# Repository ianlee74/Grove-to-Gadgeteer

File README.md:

Grove-to-Gadgeteer
==================

A project for the creation of a modules and drivers for adapting Grove modules for use with Gadgeteer.

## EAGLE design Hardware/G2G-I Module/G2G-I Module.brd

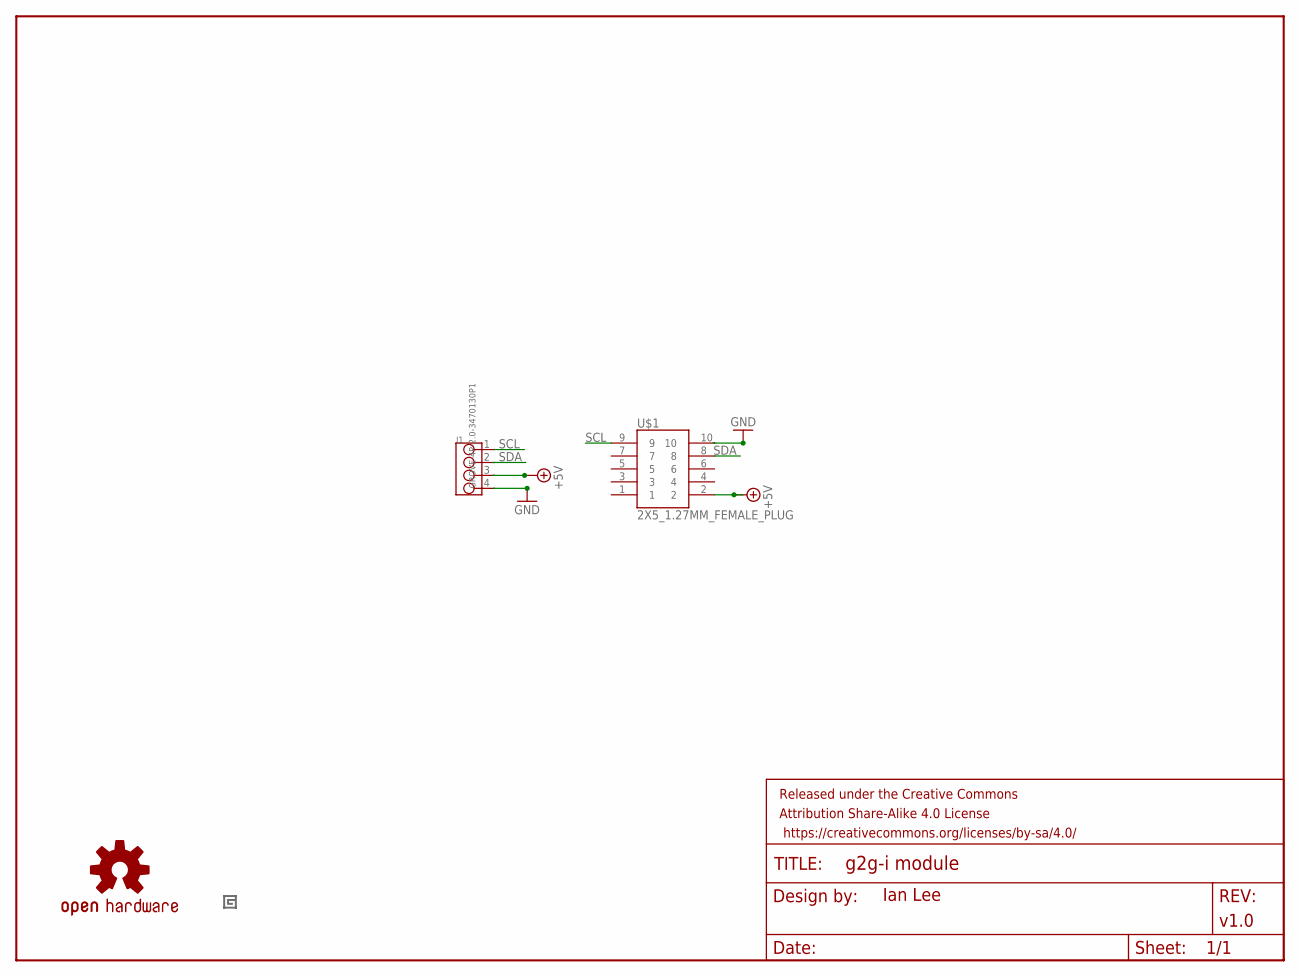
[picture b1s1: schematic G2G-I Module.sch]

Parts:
FRAME1: FRAME-LETTERNO_PACKAGE; DUMMY
J1: GROVE-4P-2.0-3470130P1; 4P-2.0
LOGO1: OSHW-LOGOS; OSHW-LOGO-S
U$1: 2X5_1.27MM_FEMALE_PLUG
U$2: GADGETEER_LOGO_SMALL

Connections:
+5V: J1.3, U$1.2
GND: J1.4, U$1.10
SCL: J1.1, U$1.9
SDA: J1.2, U$1.8

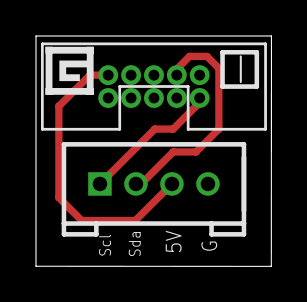
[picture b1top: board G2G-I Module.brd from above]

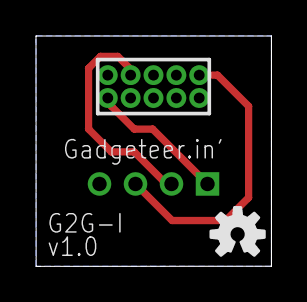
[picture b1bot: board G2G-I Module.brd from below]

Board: 2 copper layers, 13.1 x 12.8 mm, 5 parts (2 on the bottom side), 4 nets.

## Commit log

2015-01-02 Initial commit.
2015-01-02 Added initial schematic of GSG-U module (using Gadgeteer socket instead of plug...).
2015-01-11 First draft of G2G-U before ground plane.
2015-01-12 Added ground plane to G2G-U board.
2015-01-13 Added G2G-X module schematics & board.
2015-01-21 Added frames to the U and X module schematics.
2015-01-21 Added G2G-A and G2G-I modules.
2015-01-21 Passed Seeed Studio dru tests.
2015-01-21 Reduced the size of the G logo.
2015-01-21 Created Gerber files for v1.0 to send to Seeed.
2015-01-23 Added gerbmerge panel configs.
2015-01-23 Rotated the G plug 180 degrees.
2015-01-28 Replaced all 'G' logos with a new part for the logo.
2015-02-02 Adding Altium files and panel created by Justin Wilson.

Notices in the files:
parts and their libraries:
SparkFun-Aesthetics: Licensing: Creative Commons ShareAlike 4.0 International - https://creativecommons.org/licenses/by-sa/4.0
SparkFun-Aesthetics: Released under the Creative Commons Attribution Share-Alike 4.0 License
SparkFun-Aesthetics: https://creativecommons.org/licenses/by-sa/4.0
